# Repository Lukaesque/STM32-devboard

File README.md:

Experimental STM32 devboard using the STM32F103C8T6 chip.

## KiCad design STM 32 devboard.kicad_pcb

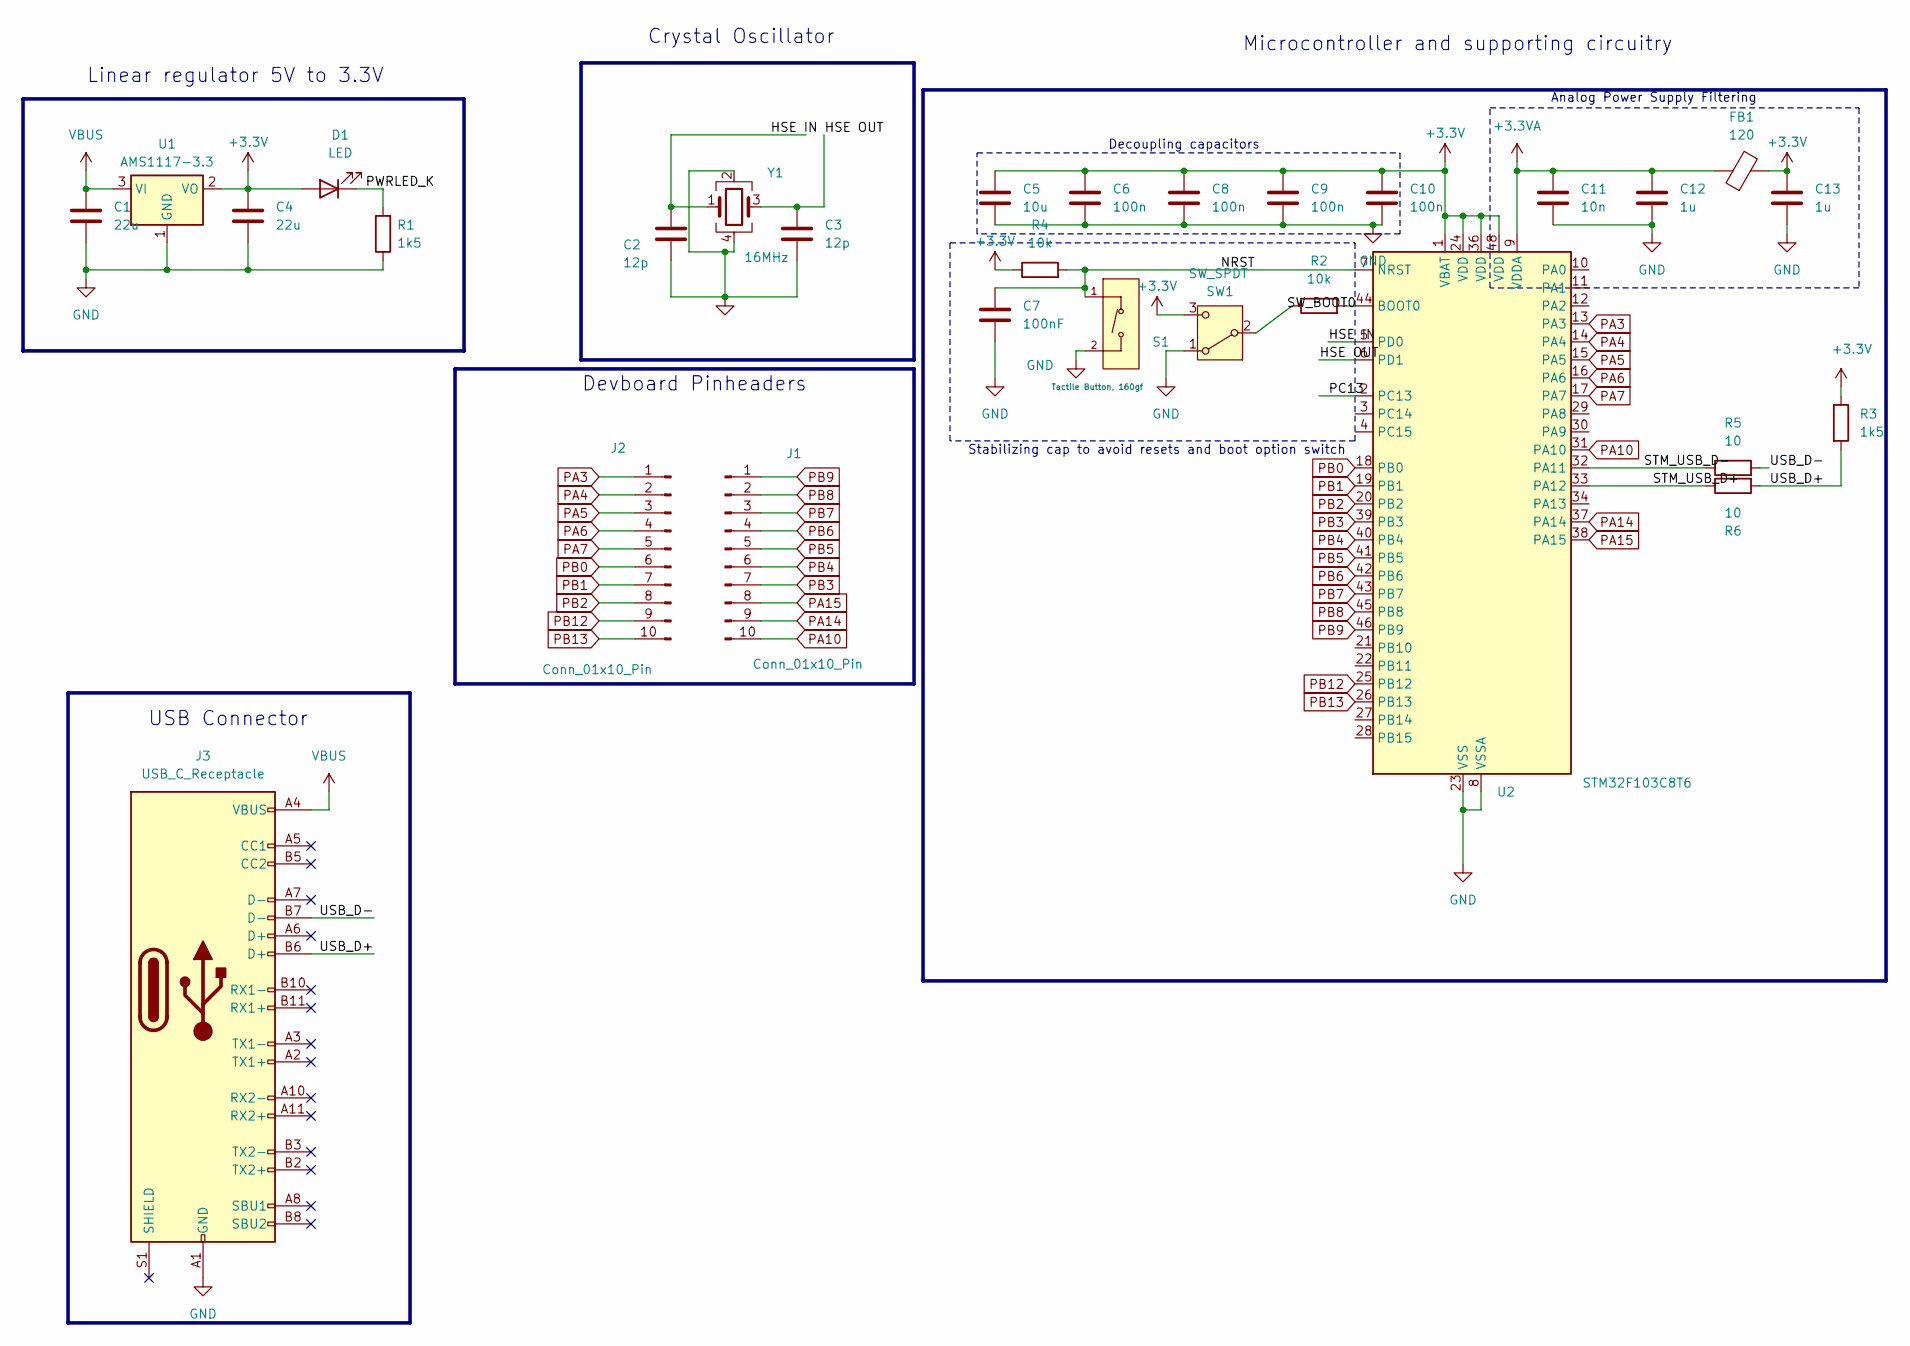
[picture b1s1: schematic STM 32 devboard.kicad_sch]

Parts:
C1, C4: 22u; C_0805_2012Metric
C2, C3: 12p; C_0402_1005Metric
C5: 10u; C_0603_1608Metric
C6, C8, C9, C10: 100n; C_0402_1005Metric
C7: 100nF; C_0402_1005Metric
C11: 10n; C_0402_1005Metric
C12, C13: 1u; C_0402_1005Metric
D1: LED; LED_0805_2012Metric
FB1: 120; C_0201_0603Metric
J1, J2: Conn_01x10_Pin; PinHeader_1x10_P2.54mm_Vertical
J3: USB_C_Receptacle; USB_C_Receptacle_GCT_USB4110
R1, R3: 1k5; R_0402_1005Metric
R2, R4: 10k; R_0402_1005Metric
R5, R6: 10; R_0402_1005Metric
S1: Tactile Button, 160gf; SW_Tactile_SPST_NO_Straight_CK_PTS636Sx25SMTRLFS; Voltage Rating (Dc) 12V; Part TS-1088-AR02016; LCSC C720477
SW1: SW_SPDT; Switch !!!!
U1: AMS1117-3.3; SOT-223-3_TabPin2
U2: STM32F103C8T6; LQFP-48_7x7mm_P0.5mm; Operating Voltage Range 2V~3.6V; Low Voltage Detection T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 2V~3.6V; Part STM32F103C8T6; LCSC C8734
Y1: 16MHz; Crystal_SMD_3225-4Pin_3.2x2.5mm

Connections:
+3.3V: C4.1, C5.1, C6.1, C8.1, C9.1, C10.1, C13.1, D1.2 (A), FB1.2, R3.1, R4.1, SW1.3 (C), U1.2 (VO), U2.1 (VBAT), U2.24 (VDD), U2.36 (VDD), U2.48 (VDD)
+3.3VA: C11.1, C12.1, FB1.1, U2.9 (VDDA)
/HSE IN: C2.1, U2.5 (PD0), Y1.1
/HSE OUT: C3.1, U2.6 (PD1), Y1.3
/NRST: C7.1, R4.2, S1.1 (A), U2.7 (NRST)
/PC13: U2.2 (PC13)
/PWRLED_K: D1.1 (K), R1.2
/STM_USB_D+: R6.1, U2.33 (PA12)
/STM_USB_D-: R5.1, U2.32 (PA11)
/SW_BOOT0: R2.1, SW1.2 (B)
/USB_D+: J3.B6 (D+), R3.2, R6.2
/USB_D-: J3.B7 (D-), R5.2
GND: C1.2, C2.2, C3.2, C4.2, C5.2, C6.2, C7.2, C8.2, C9.2, C10.2, C11.2, C12.2, C13.2, J3.A1 (GND), J3.A12 (GND), J3.B1 (GND), J3.B12 (GND), R1.1, S1.2 (B), SW1.1 (A), U1.1 (GND), U2.8 (VSSA), U2.23 (VSS), U2.35 (VSS), U2.47 (VSS), Y1.2, Y1.4
unnamed: R2.2, U2.44 (BOOT0)
PA3: J2.1, U2.13 (PA3)
PA4: J2.2, U2.14 (PA4)
PA5: J2.3, U2.15 (PA5)
PA6: J2.4, U2.16 (PA6)
PA7: J2.5, U2.17 (PA7)
PA10: J1.10, U2.31 (PA10)
PA14: J1.9, U2.37 (PA14)
PA15: J1.8, U2.38 (PA15)
PB0: J2.6, U2.18 (PB0)
PB1: J2.7, U2.19 (PB1)
PB2: J2.8, U2.20 (PB2)
PB3: J1.7, U2.39 (PB3)
PB4: J1.6, U2.40 (PB4)
PB5: J1.5, U2.41 (PB5)
PB6: J1.4, U2.42 (PB6)
PB7: J1.3, U2.43 (PB7)
PB8: J1.2, U2.45 (PB8)
PB9: J1.1, U2.46 (PB9)
PB12: J2.9, U2.25 (PB12)
PB13: J2.10, U2.26 (PB13)
VBUS: C1.1, J3.A4 (VBUS), J3.A9 (VBUS), J3.B4 (VBUS), J3.B9 (VBUS), U1.3 (VI)

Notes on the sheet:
Stabilizing cap to avoid resets and boot option switch
Microcontroller and supporting circuitry
Analog Power Supply Filtering
USB Connector
Devboard Pinheaders
Crystal Oscillator
Linear regulator 5V to 3.3V
Decoupling capacitors

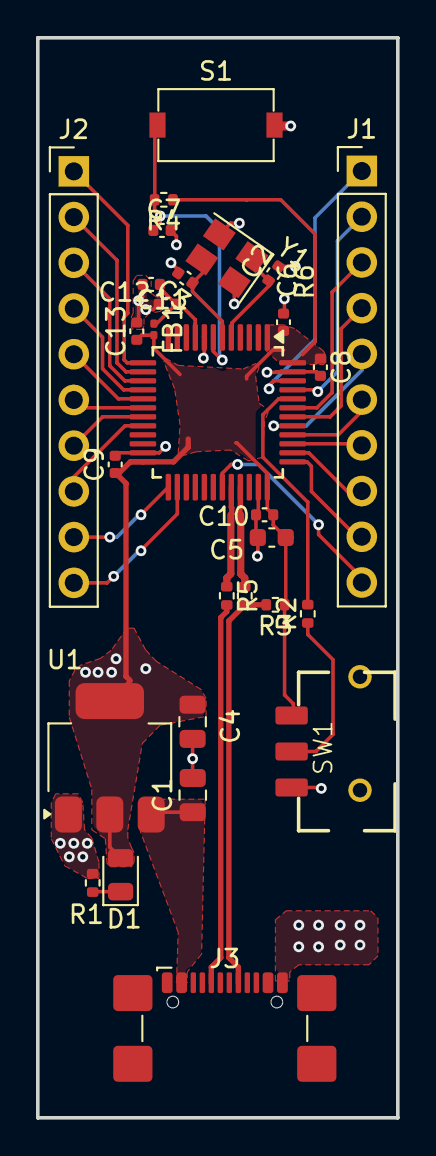
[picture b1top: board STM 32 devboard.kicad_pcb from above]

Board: 2 copper layers, 20.0 x 60.0 mm, 29 parts (0 on the bottom side), 34 nets.

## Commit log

2025-07-24 Initially uploading all of my files
2025-07-24 Removal of temporary files
2025-08-15 Test on linux
2025-08-15 Added USB-C port.
